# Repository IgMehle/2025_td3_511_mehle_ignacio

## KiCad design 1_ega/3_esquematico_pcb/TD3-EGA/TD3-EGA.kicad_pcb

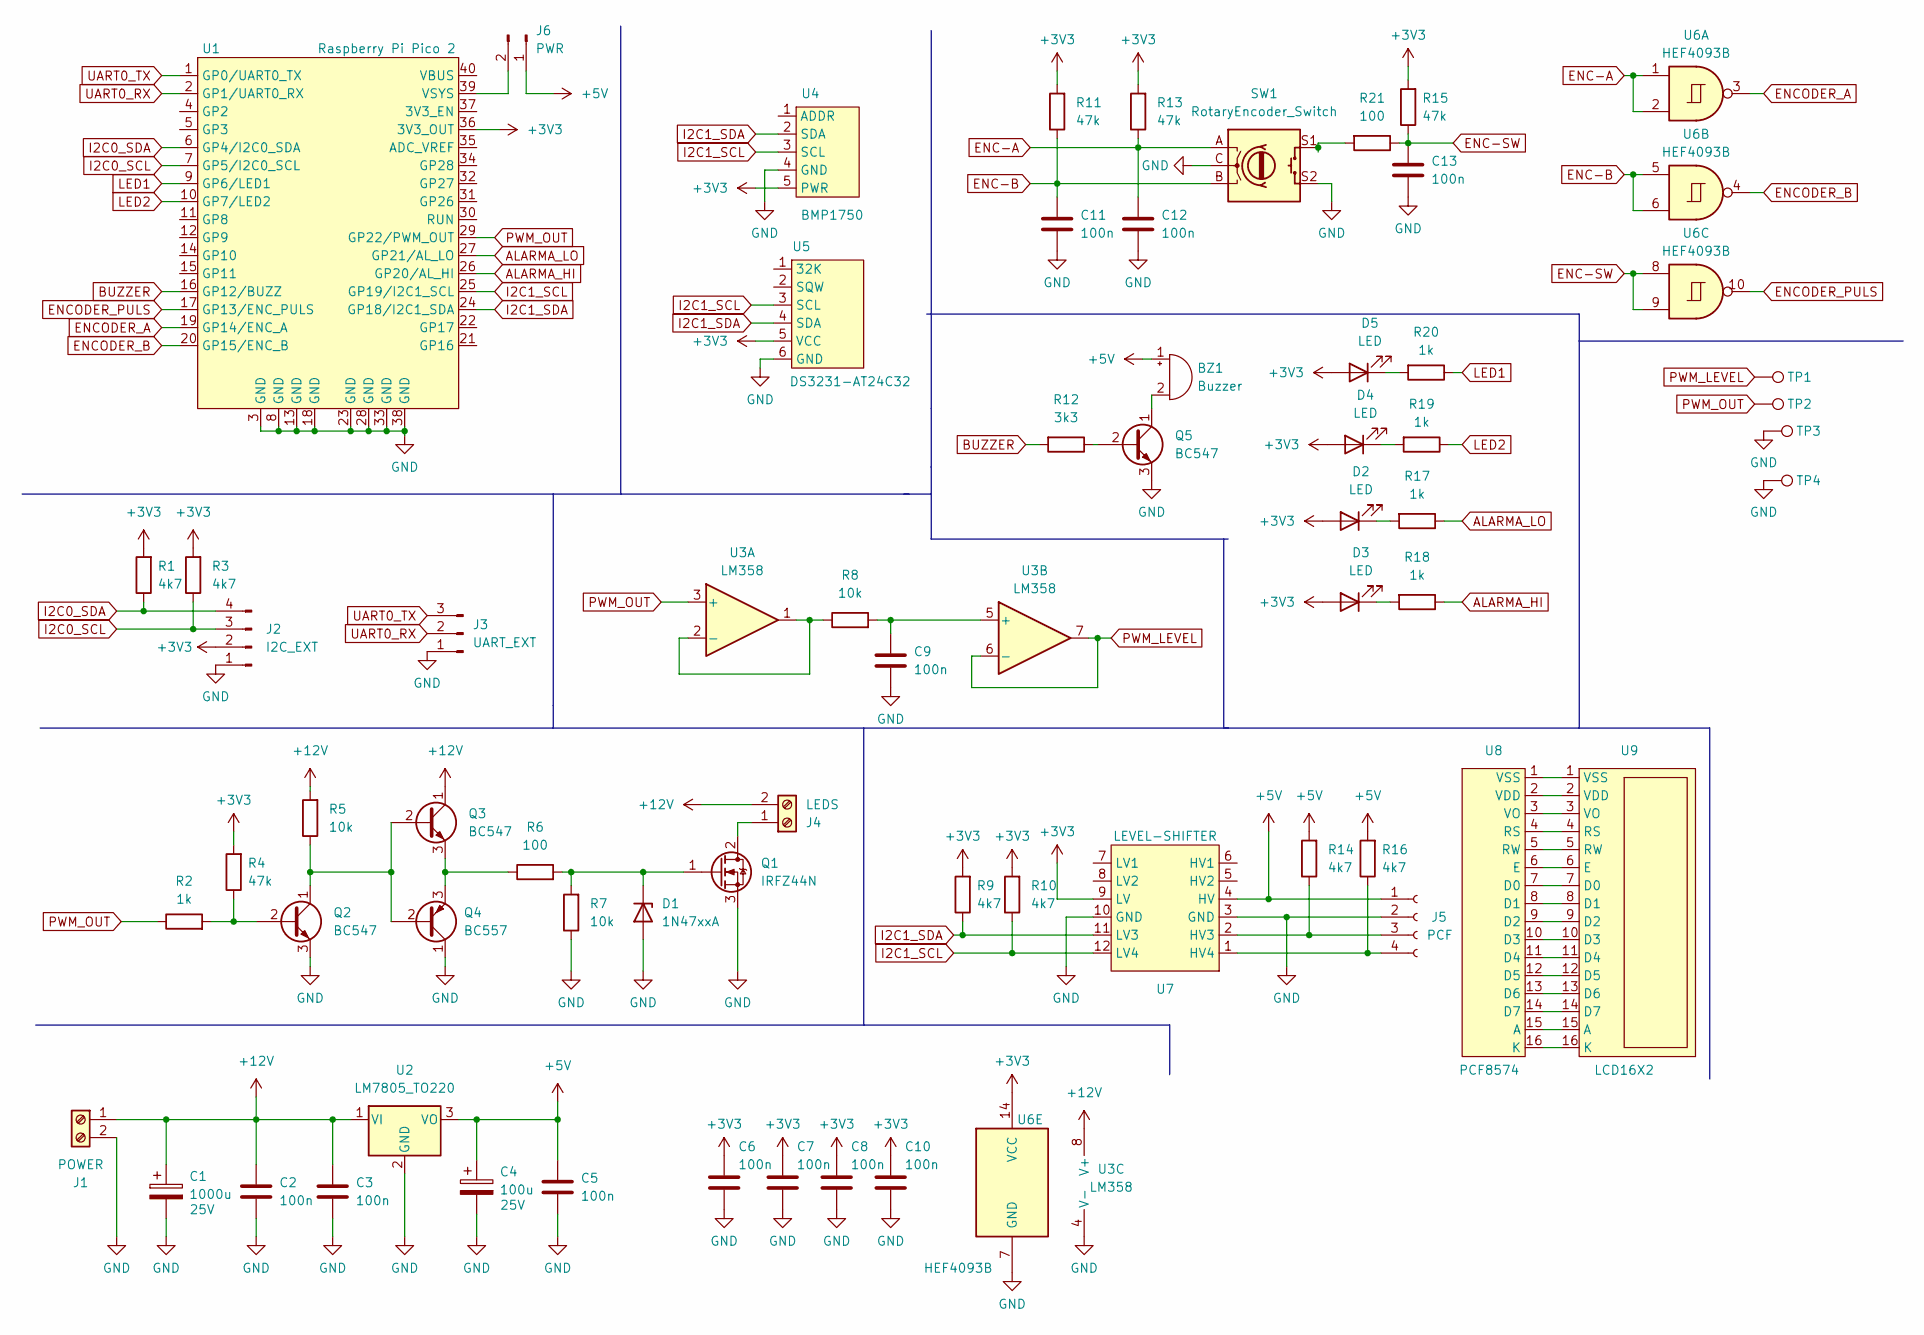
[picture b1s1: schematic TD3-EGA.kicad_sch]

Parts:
BZ1: Buzzer; Buzzer_12x9.5RM7.6
C1: 1000u; CP_Radial_D14.0mm_P5.00mm
C2, C3, C5, C6, C7, C8, C9, C10, C11, C12, C13: 100n; C_Rect_L7.2mm_W3.0mm_P5.00mm_FKS2_FKP2_MKS2_MKP2
C4: 100u; CP_Radial_D8.0mm_P2.50mm
D1: 1N47xxA; D_DO-41_SOD81_P10.16mm_Horizontal
D2, D3, D4, D5: LED; LED_D5.0mm
J1: POWER; TerminalBlock_Phoenix_MKDS-1,5-2_1x02_P5.00mm_Horizontal
J2: I2C_EXT; PinHeader_1x04_P2.54mm_Vertical
J3: UART_EXT; PinHeader_1x03_P2.54mm_Vertical
J4: LEDS; TerminalBlock_Phoenix_MKDS-1,5-2_1x02_P5.00mm_Horizontal
J5: PCF; PinSocket_1x04_P2.54mm_Vertical
J6: PWR; PinHeader_1x02_P2.54mm_Vertical
Q1: IRFZ44N; TO-220-3_Vertical
Q2, Q3, Q5: BC547; TO-92_HandSolder
Q4: BC557; TO-92_HandSolder
R1, R3, R9, R10, R14, R16: 4k7; R_Axial_DIN0207_L6.3mm_D2.5mm_P10.16mm_Horizontal
R2, R17, R18, R19, R20: 1k; R_Axial_DIN0207_L6.3mm_D2.5mm_P10.16mm_Horizontal
R4, R11, R13, R15: 47k; R_Axial_DIN0207_L6.3mm_D2.5mm_P10.16mm_Horizontal
R5, R7, R8: 10k; R_Axial_DIN0207_L6.3mm_D2.5mm_P10.16mm_Horizontal
R6, R21: 100; R_Axial_DIN0207_L6.3mm_D2.5mm_P10.16mm_Horizontal
R12: 3k3; R_Axial_DIN0207_L6.3mm_D2.5mm_P10.16mm_Horizontal
SW1: RotaryEncoder_Switch; RotaryEncoder_Alps_EC11E-Switch_Vertical_H20mm
TP1, TP2, TP3, TP4: TestPoint; TestPoint_Loop_D2.50mm_Drill1.0mm
U1: Raspberry Pi Pico 2; PICO2
U2: LM7805_TO220; TO-220-3_Vertical
U3: LM358; DIP-8_W7.62mm
U4: BMP1750; BH1750
U5: DS3231-AT24C32; PinSocket_1x06_P2.54mm_Vertical
U6: HEF4093B; DIP-14_W7.62mm
U7: LEVEL-SHIFTER; LVL-SHIFTER
U8: PCF8574; PCF85741
U9: LCD16X2; PinSocket_1x16_P2.54mm_Vertical

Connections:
+3V3: C6.1, C7.1, C8.1, C10.1, D2.2 (A), D3.2 (A), D4.2 (A), D5.2 (A), J2.2, R1.2, R3.2, R4.2, R9.2, R10.2, R11.2, R13.2, R15.2, U1.36 (3V3_OUT), U4.5 (PWR), U5.5 (VCC), U6.14 (VCC), U7.9 (LV)
+5V: BZ1.1 (+), C4.1, C5.1, J5.1, J6.1, R14.2, R16.2, U2.3 (VO), U7.4 (HV)
+12V: C1.1, C2.1, C3.1, J1.1, J4.2, Q3.1 (C), R5.2, U2.1 (VI), U3.8 (V+)
ALARMA_HI: R18.1, U1.26 (GP20/AL_HI)
ALARMA_LO: R17.1, U1.27 (GP21/AL_LO)
BUZZER: R12.2, U1.16 (GP12/BUZZ)
ENC-A: C12.1, R13.1, SW1.A, U6.1, U6.2
ENC-B: C11.1, R11.1, SW1.B, U6.5, U6.6
ENC-SW: C13.1, R15.1, R21.1, U6.8, U6.9
ENCODER_A: U1.19 (GP14/ENC_A), U6.3
ENCODER_B: U1.20 (GP15/ENC_B), U6.4
ENCODER_PULS: U1.17 (GP13/ENC_PULS), U6.10
GND: C1.2, C2.2, C3.2, C4.2, C5.2, C6.2, C7.2, C8.2, C9.2, C10.2, C11.2, C12.2, C13.2, D1.2 (A), J1.2, J2.1, J3.1, J5.2, Q1.3 (S), Q2.3 (E), Q4.1 (C), Q5.3 (E), R7.1, SW1.C, SW1.S2, TP3.1, TP4.1, U1.3 (GND), U1.8 (GND), U1.13 (GND), U1.18 (GND), U1.23 (GND), U1.28 (GND), U1.33 (GND), U1.38 (GND), U2.2 (GND), U3.4 (V-), U4.4 (GND), U5.6 (GND), U6.7 (GND), U7.3 (GND), U7.10 (GND); also elsewhere on the board
I2C0_SCL: J2.3, R3.1, U1.7 (GP5/I2C0_SCL)
I2C0_SDA: J2.4, R1.1, U1.6 (GP4/I2C0_SDA)
I2C1_SCL: R10.1, U1.25 (GP19/I2C1_SCL), U4.3 (SCL), U5.3 (SCL), U7.12 (LV4)
I2C1_SDA: R9.1, U1.24 (GP18/I2C1_SDA), U4.2 (SDA), U5.4 (SDA), U7.11 (LV3)
LED1: R20.1, U1.9 (GP6/LED1)
LED2: R19.1, U1.10 (GP7/LED2)
unnamed: BZ1.2 (-), Q5.1 (C)
unnamed: D1.1 (K), Q1.1 (G), R6.2, R7.2
unnamed: D2.1 (K), R17.2
unnamed: D3.1 (K), R18.2
unnamed: D4.1 (K), R19.2
unnamed: D5.1 (K), R20.2
unnamed: J4.1, Q1.2 (D)
unnamed: J5.3, R14.1, U7.2 (HV3)
unnamed: J5.4, R16.1, U7.1 (HV4)
unnamed: J6.2, U1.39 (VSYS)
unnamed: Q2.2 (B), R2.2, R4.1
unnamed: Q2.1 (C), Q3.2 (B), Q4.2 (B), R5.1
unnamed: Q3.3 (E), Q4.3 (E), R6.1
unnamed: Q5.2 (B), R12.1
unnamed: R21.2, SW1.S1
unnamed: R8.1, U3.1, U3.2 (-)
unnamed: C9.1, R8.2, U3.5 (+)
unnamed: U8.15 (A), U9.15 (A)
unnamed: U8.7 (D0), U9.7 (D0)
unnamed: U8.8 (D1), U9.8 (D1)
unnamed: U8.9 (D2), U9.9 (D2)
unnamed: U8.10 (D3), U9.10 (D3)
unnamed: U8.11 (D4), U9.11 (D4)
unnamed: U8.12 (D5), U9.12 (D5)
unnamed: U8.13 (D6), U9.13 (D6)
unnamed: U8.14 (D7), U9.14 (D7)
unnamed: U8.6 (E), U9.6 (E)
unnamed: U8.16 (K), U9.16 (K)
unnamed: U8.4 (RS), U9.4 (RS)
unnamed: U8.5 (RW), U9.5 (RW)
unnamed: U8.2 (VDD), U9.2 (VDD)
unnamed: U8.3 (VO), U9.3 (VO)
unnamed: U8.1 (VSS), U9.1 (VSS)
PWM_LEVEL: TP1.1, U3.6 (-), U3.7
PWM_OUT: R2.1, TP2.1, U1.29 (GP22/PWM_OUT), U3.3 (+)
UART0_RX: J3.2, U1.2 (GP1/UART0_RX)
UART0_TX: J3.3, U1.1 (GP0/UART0_TX)

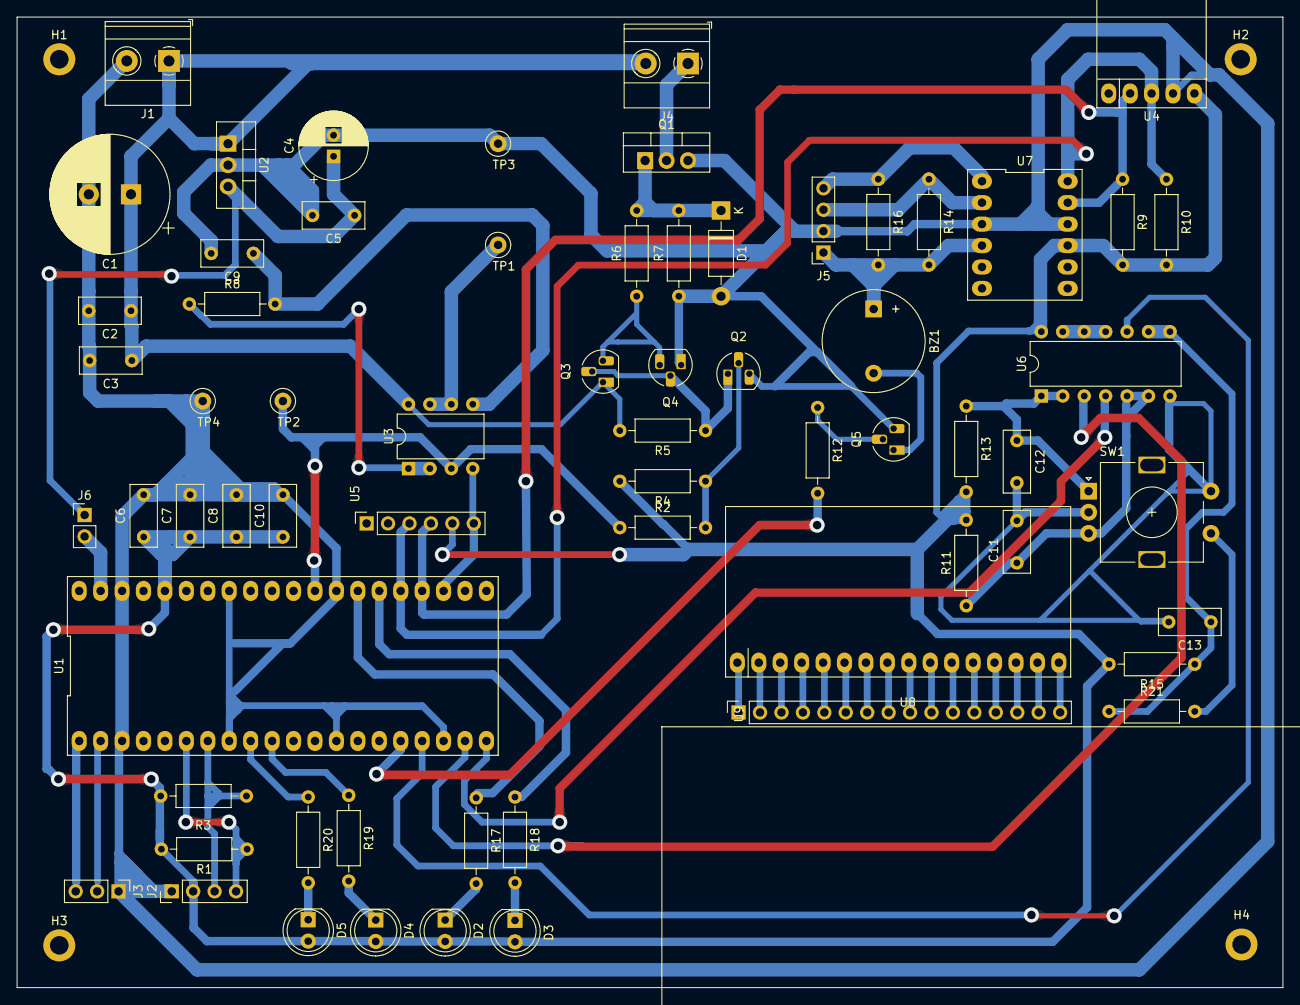
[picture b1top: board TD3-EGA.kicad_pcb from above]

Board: 2 copper layers, 150.0 x 115.0 mm, 69 parts (0 on the bottom side), 56 nets.

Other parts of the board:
H1, H2, H3, H4: MountingHole_2.2mm_M2_DIN965_Pad

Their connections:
GND: H1.1, H2.2, H3.3, H4.4; also elsewhere on the board

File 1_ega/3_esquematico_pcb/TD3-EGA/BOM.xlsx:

Reference | Value | Footprint | Qty | OK
BZ1 | Buzzer | Buzzer_Beeper:Buzzer_12x9.5RM7.6 | 1
C1 | 1000u | Capacitor_THT:CP_Radial_D14.0mm_P5.00mm | 1
C2,C3,C5,C6,C7,C8,C9,C10,C11,C12,C13 | 100n | Capacitor_THT:C_Rect_L7.2mm_W3.0mm_P5.00mm_FKS2_FKP2_MKS2_MKP2 | 11
C4 | 100u | Capacitor_THT:CP_Radial_D8.0mm_P2.50mm | 1
D1 | 1N47xxA | Diode_THT:D_DO-41_SOD81_P10.16mm_Horizontal | 1
D2,D3,D4,D5 | LED | LED_THT:LED_D5.0mm | 4
J1 | POWER | TerminalBlock_Phoenix:TerminalBlock_Phoenix_MKDS-1,5-2_1x02_P5.00mm_Horizontal | 1
J2 | I2C_EXT | Connector_PinHeader_2.54mm:PinHeader_1x04_P2.54mm_Vertical | 1
J3 | UART_EXT | Connector_PinHeader_2.54mm:PinHeader_1x03_P2.54mm_Vertical | 1
J4 | LEDS | TerminalBlock_Phoenix:TerminalBlock_Phoenix_MKDS-1,5-2_1x02_P5.00mm_Horizontal | 1
J5 | PCF | Connector_PinSocket_2.54mm:PinSocket_1x04_P2.54mm_Vertical | 1
J6 | PWR | Connector_PinHeader_2.54mm:PinHeader_1x02_P2.54mm_Vertical | 1
Q1 | IRFZ44N | Package_TO_SOT_THT:TO-220-3_Vertical | 1
Q2,Q3,Q5 | BC547 | Package_TO_SOT_THT:TO-92_HandSolder | 3
Q4 | BC557 | Package_TO_SOT_THT:TO-92_HandSolder | 1
R1,R3,R9,R10,R14,R16 | 4k7 | Resistor_THT:R_Axial_DIN0207_L6.3mm_D2.5mm_P10.16mm_Horizontal | 6
R2,R17,R18,R19,R20 | 1k | Resistor_THT:R_Axial_DIN0207_L6.3mm_D2.5mm_P10.16mm_Horizontal | 5
R4,R11,R13,R15 | 47k | Resistor_THT:R_Axial_DIN0207_L6.3mm_D2.5mm_P10.16mm_Horizontal | 4
R5,R7,R8 | 10k | Resistor_THT:R_Axial_DIN0207_L6.3mm_D2.5mm_P10.16mm_Horizontal | 3
R6,R21 | 100 | Resistor_THT:R_Axial_DIN0207_L6.3mm_D2.5mm_P10.16mm_Horizontal | 2
R12 | 3k3 | Resistor_THT:R_Axial_DIN0207_L6.3mm_D2.5mm_P10.16mm_Horizontal | 1
SW1 | RotaryEncoder_Switch | Rotary_Encoder:RotaryEncoder_Alps_EC11E-Switch_Vertical_H20mm | 1
TP1,TP2,TP3,TP4 | TestPoint | TestPoint:TestPoint_Loop_D2.50mm_Drill1.0mm | 4
U1 | Raspberry Pi Pico 2 | TD3-EGA:PICO2 | 1
U2 | LM7805_TO220 | Package_TO_SOT_THT:TO-220-3_Vertical | 1
U3 | LM358 | Package_DIP:DIP-8_W7.62mm | 1
U4 | BMP1750 | TD3-EGA:BH1750 | 1
U5 | DS3231-AT24C32 | Connector_PinSocket_2.54mm:PinSocket_1x06_P2.54mm_Vertical | 1
U6 | HEF4093B | Package_DIP:DIP-14_W7.62mm | 1
U7 | LEVEL-SHIFTER | TD3-EGA:LVL-SHIFTER | 1
U8 | PCF8574 | TD3-EGA:PCF85741 | 1
U9 | LCD16X2 | Connector_PinSocket_2.54mm:PinSocket_1x16_P2.54mm_Vertical | 1

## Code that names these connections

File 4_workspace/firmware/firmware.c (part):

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#include "semphr.h"

// PINOUT
#define I2C1_SDA_PIN    18
#define I2C1_SCL_PIN    19
#define PWM_OUT_PIN     22
#define ENC_A_PIN       14
#define ENC_B_PIN       15
#define PULS_PIN        13
#define LED1_PIN        6
#define LED2_PIN        7
#define LED_RUN_PIN     25
#define AL_LO_PIN       20
#define AL_HI_PIN       21
#define BUZZER_PIN      12
// CONSTANTES
#define LUX_TIME        25

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#define ENC_A_FALL      4
#define ENC_B_FALL      5
// MACROS SALIDAS DIGITALES
#define LED1_ON         gpio_put(LED1_PIN, false)
#define LED1_OFF        gpio_put(LED1_PIN, true)
#define LED2_ON         gpio_put(LED2_PIN, false)
#define LED2_OFF        gpio_put(LED2_PIN, true)
#define ALARMA_LO_ON    gpio_put(AL_LO_PIN, false)
#define ALARMA_LO_OFF   gpio_put(AL_LO_PIN, true)
#define ALARMA_HI_ON    gpio_put(AL_HI_PIN, false)
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void setup_pwm(float duty)
{
    //Cargo el slice fisico del pin
    uint slice_num = pwm_gpio_to_slice_num(PWM_OUT_PIN);
    //Frec de clock de la pico 2
    const float clock_freq = 125000000.f;              
    const float freq = 1000.0;
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    static float duty_f = 0.0;

    //Pongo el pin como pwm
    gpio_set_function(PWM_OUT_PIN, GPIO_FUNC_PWM);
    //Calculo con precision de 16 bits de la frec que se quiere--65536        
    //divider = clock_freq / (freq * 8192);    
    pwm_set_clkdiv(slice_num, divider);
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    pwm_set_wrap(slice_num, 8191);                 
    //Calcula el duty cycle--65536

    pwm_set_gpio_level(PWM_OUT_PIN, duty * 8192);
    // Habilita el PWM en el pin            
    pwm_set_enabled(slice_num, true);
}
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
    // I2C INIT
    i2c_init(i2c1, I2C1_FREQ);
    gpio_set_function(I2C1_SDA_PIN, GPIO_FUNC_I2C);
    gpio_set_function(I2C1_SCL_PIN, GPIO_FUNC_I2C);
    // Pongo pullups a 3V3
    //gpio_pull_up(I2C1_SDA_PIN);
    //gpio_pull_up(I2C1_SCL_PIN);

    // Inicializo LCD
    lcd_init(i2c1, LCD_ADDR);
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    gpio_put(LED_RUN_PIN, true);

    // Init LED 1
    gpio_init(LED1_PIN);
    gpio_set_dir(LED1_PIN, true);
    gpio_put(LED1_PIN, true);

    // Init LED 2
    gpio_init(LED2_PIN);
    gpio_set_dir(LED2_PIN, true);
    gpio_put(LED2_PIN, true);

    // Init ALARMA LO
    gpio_init(AL_LO_PIN);
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    gpio_put(AL_HI_PIN, true);

    // Init BUZZER
    gpio_init(BUZZER_PIN);
    gpio_set_dir(BUZZER_PIN, true);
    gpio_put(BUZZER_PIN, false);

    // Creo semaforos binarios y los libero
    vSemaphoreCreateBinary(sRTC);
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
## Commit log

2025-05-28 Cambios locales
2025-06-02 Primer consigna de TP
2025-06-02 Segunda consigna de TP3
2025-06-25 Work in progress
2025-07-02 BH1750 library working
2025-07-04 luxometro y rtc working
2025-07-04 agrego cambios
2025-07-04 Entrega de EGA v1
2025-07-11 AT24C32 OK, trabajando en el encoder
2025-07-15 Creo proyecto de prueba de freertos en 1_ega/2_workspace
2025-07-19 Sigo trabajando en el encoder
2025-07-19 Entrega EGA V2
2025-07-27 Cambios
2025-07-27 working...
2025-07-29 Save to change branch
2025-07-31 trabajando en menu settings
2025-08-03 Modifico lib ds3231, probar menu
2025-08-04 Lee pulsador, entra al menu y se clava
2025-08-04 Menu funcionando, cambios en irq
2025-08-07 Eeprom actualizada con queueset
2025-08-08 Avances de prueba, modificar task_EEPROM()
2025-08-09 Guardo cambios
2025-08-11 task_EEPROM modif, ver task_RTC
2025-08-12 Func basico, arreglar eeprom, refresh y consola
2025-08-13 Backup, task_EEPROM() vas a morir
2025-08-14 eeprom_write() y eeprom_read() modificadas
2025-08-15 task_EEPROM() anda
2025-08-15 bh1750 agrego modos
2025-08-15 b2s() y s2b() dentro de task eeprom
2025-08-16 task_Consola() funcional, revisar dump size y erase
2025-08-21 PID preliminar funcionando
2025-08-23 PID rapido PI lento empiricos
2025-08-24 Agrego funciones dump y clear settings al menu
2025-08-25 autotune() falta ajustar, corregir bug de index en task_eeprom()
2025-08-25 Limpio codigo
2025-08-27 Version aprobable
2025-08-27 Segunda entrega de TP4
2025-08-28 Entrega EGA/v3
2025-10-10 Primer consigna de TP5
2025-10-10 Segunda consigna de TP5
2025-10-10 Proyecto de kicad borrado
2025-10-26 Ultimo firmware EGA/V3
2025-10-27 cli v01 funcional
2025-10-31 Primeros apuntes en w10
2025-10-31 Archivos movidos
2025-10-31 Agrego firmware a workspace
2025-10-31 Pruebas 1C agregadas
2025-11-01 uart_set
2025-11-02 Funciones uart testing con pico 1
2025-11-02 uart-test, CONFIG_USE_DYNAMIC_ALLOC ON en cmakelist
2025-11-02 Funciones con uart diseniadas
2025-11-02 Probando recepcion en Pico 2
2025-11-02 testeando
2025-11-03 literalmente viendo que onda la cli
2025-11-05 Mejora en rx de log
2025-11-07 uart_set_rtc() funcional
2025-11-07 funciones uart_test -> firmware
2025-11-07 agrego ack en set()
2025-11-08 ega + uart-test - firmware-egb
2025-11-08 set lux basico funcional
2025-11-09 uart no corre probe()
2025-11-09 reestructuracion
2025-11-10 chardev_write_file testeada
2025-11-10 agrego clases de Linux
2025-11-12 No rompas tu codigo Nacho
2025-11-12 s_lux y overwrite/peek q_lux OK
2025-11-12 firmware-egb v1 FULL
2025-11-13 Probando uart1 no corre probe()
2025-11-15 probando modulo en pi 3, no anda
2025-11-15 add ejemplos file
2025-11-17 Chau serdev
2025-11-20 Agrego ejemplos de driver i2c en Pi
2025-11-22 Agrego tests de i2c en pico
2025-11-24 i2c_slave baremetal ok, freertos nop
2025-11-30 uart-hello funciona
2025-12-01 working on egb_uart_serdev
2025-12-06 egb_uart_serdev func ok
2025-12-07 serdev + writefile funciona
2025-12-08 cli funciona basico con rx.txt
2025-12-10 r/w ok, log file basico ok
2025-12-10 probando consola
2025-12-10 version funcional v01
2025-12-10 Rama limpia
2025-12-16 probar nuevo path, trabajando en la GUI
2025-12-16 Prueba de funciones de polling en GUI
2025-12-17 EGB funcional con GUI
2025-12-17 Entrega EGB/V1
